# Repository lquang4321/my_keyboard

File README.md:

# Keypad
A standard 17-key numpad in 5x4 config, num lock indicator LED, and a media volume knob. An Arduino Pro Micro (Atmega32u4 5V 16Mhz) is used as the MCU. 
* Author: [Quang Truong](https://github.com/lquang4321) 
* Version: 1 

Make example: 

    make my_keyboard:default
# Schematic

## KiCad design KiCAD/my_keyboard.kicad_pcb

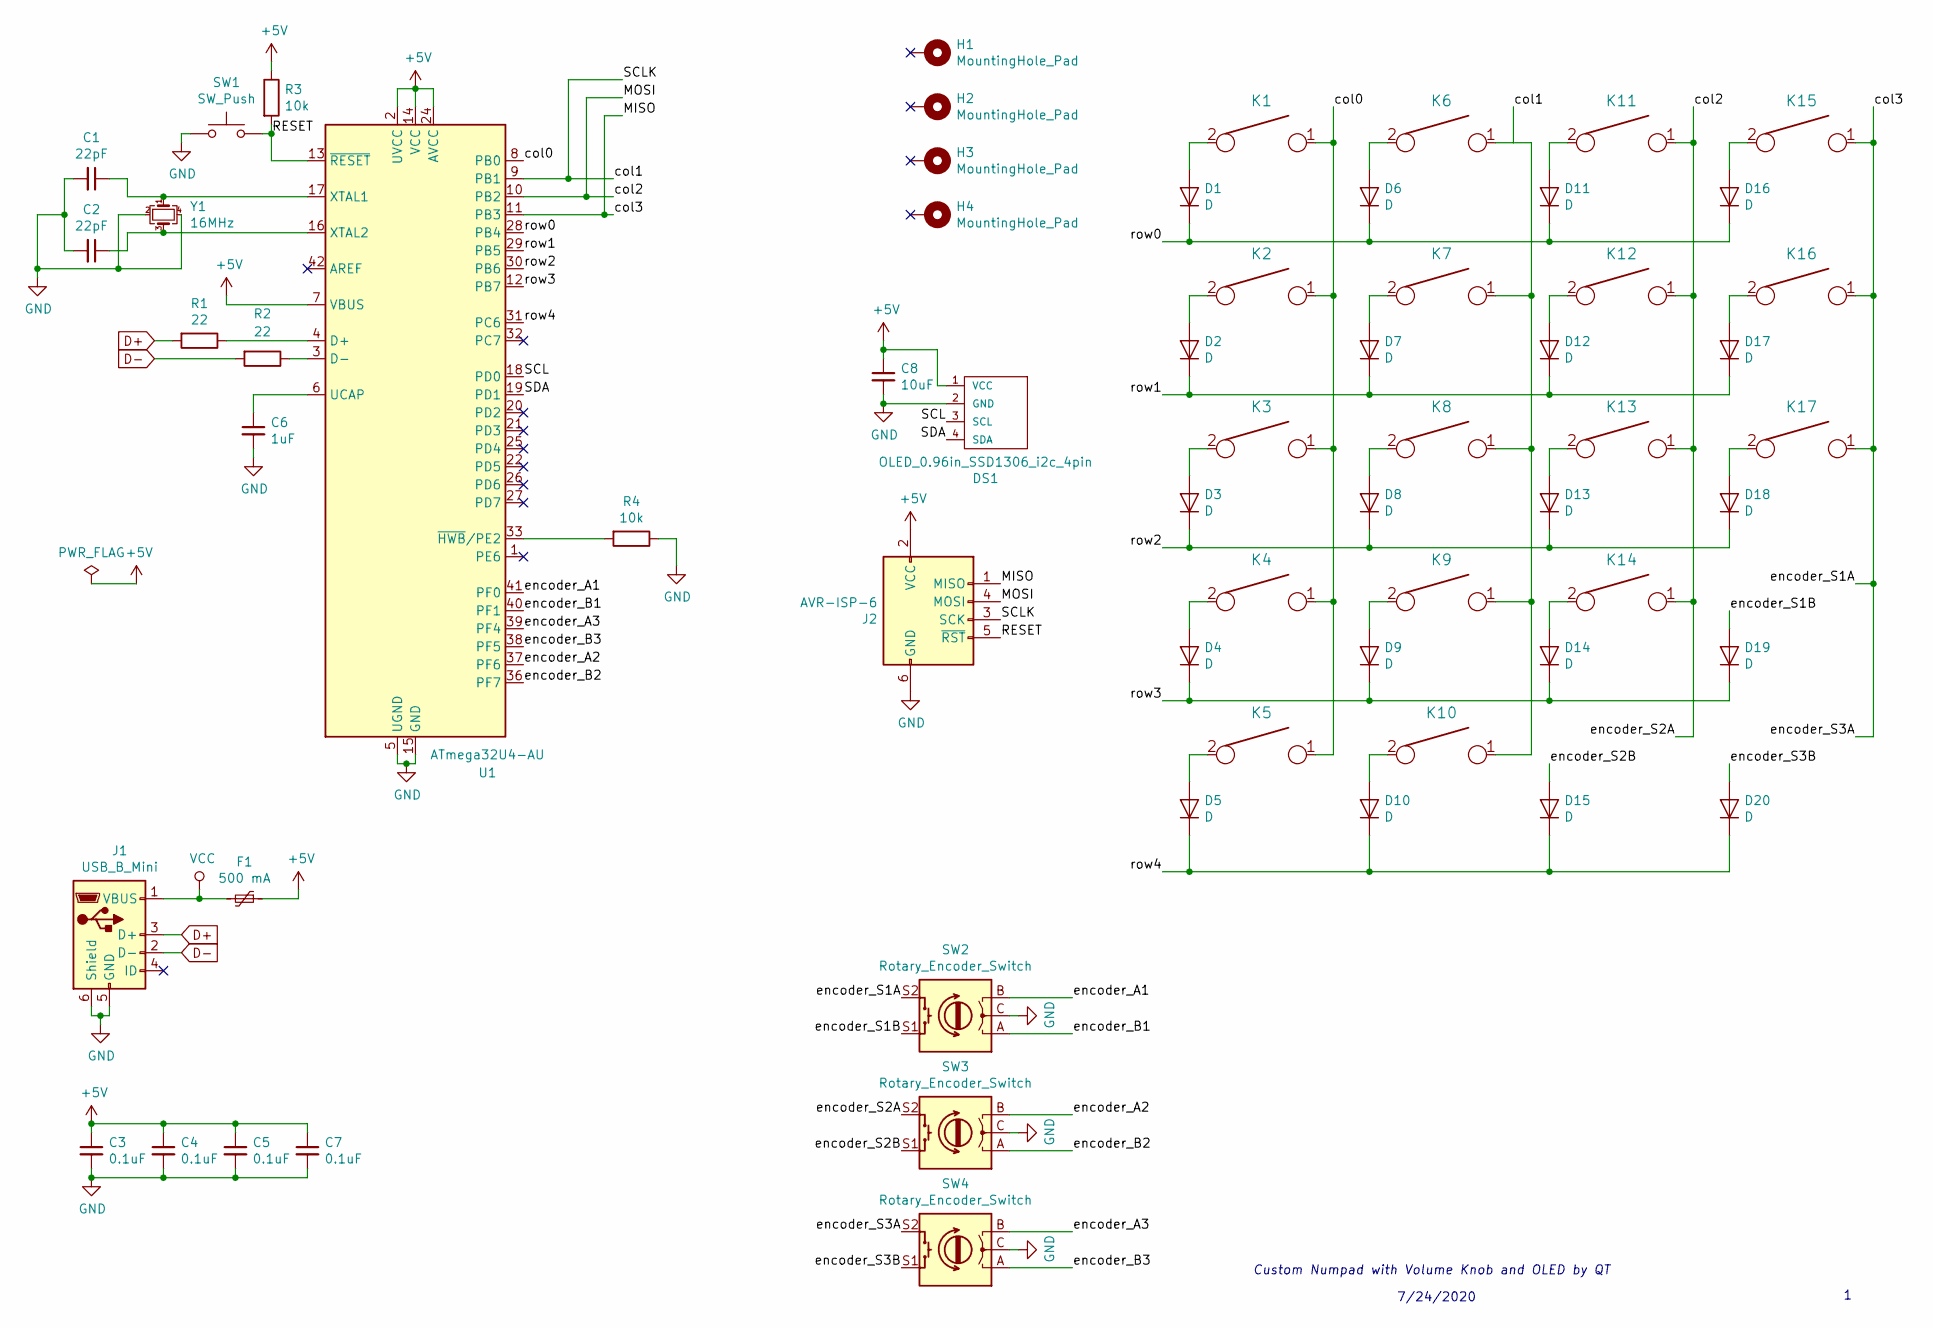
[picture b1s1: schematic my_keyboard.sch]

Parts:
C1, C2: 22pF; C_0805_2012Metric_Pad1.15x1.40mm_HandSolder; JLCPCB Parts C14663
C3, C4, C5, C7: 0.1uF; C_0805_2012Metric_Pad1.15x1.40mm_HandSolder; JLCPCB Parts C14663
C6: 1uF; C_0805_2012Metric_Pad1.15x1.40mm_HandSolder; JLCPCB Parts C15849
C8: 10uF; C_0805_2012Metric_Pad1.15x1.40mm_HandSolder; JLCPCB Parts C19702
D1, D2, D3, D4, D5, D6, D7, D8, D9, D10, D11, D12, D13, D14, D15, D16, D17, D18, D19, D20: D; D_SOD-123; JLCPCB Parts C81598
DS1: OLED_0.96in_SSD1306_i2c_4pin
F1: 500 mA; Fuse_1206_3216Metric_Pad1.42x1.75mm_HandSolder; JLCPCB Parts C151162
H1, H2, H3, H4: MountingHole_Pad; MountingHole_3.2mm_M3_Pad_Via
J1: USB_B_Mini; USB_miniB
J2: AVR-ISP-6; AVR_ICSP_3x2
K1, K2, K3, K4, K6, K7, K8, K9, K10, K11, K12, K13, K14, K15: KEYSW; SW_Cherry_MX_1.00u_PCB
K5: KEYSW; SW_Cherry_MX_2.00u_Plate
K16, K17: KEYSW; SW_Cherry_MX_2.00u_Vertical_Plate
R1, R2: 22; R_0805_2012Metric_Pad1.15x1.40mm_HandSolder; JLCPCB Parts C23345
R3, R4: 10k; R_0805_2012Metric_Pad1.15x1.40mm_HandSolder; JLCPCB Parts C25804
SW1: SW_Push; SW_PUSH_4_5.1x5.1mm; JLCPCB Parts C318884
SW2, SW3, SW4: Rotary_Encoder_Switch; RotaryEncoder_Alps_EC11E-Switch_Vertical_H20mm
U1: ATmega32U4-AU; TQFP-44_10x10mm_P0.8mm; JLCPCB Parts C44854
Y1: 16MHz; Crystal_SMD_3225-4Pin_3.2x2.5mm_HandSoldering; JLCPCB Parts C13738

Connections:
+5V: C3.1, C4.1, C5.1, C7.1, C8.1, DS1.1 (VCC), F1.1, J2.2 (VCC), R3.1, U1.2 (UVCC), U1.7 (VBUS), U1.14 (VCC), U1.24 (AVCC), U1.34 (VCC), U1.44 (AVCC)
/MISO: J2.1 (MISO), K15.1, K16.1, K17.1, SW2.S2, SW4.S2, U1.11 (PB3)
/MOSI: J2.4 (MOSI), K11.1, K12.1, K13.1, K14.1, SW3.S2, U1.10 (PB2)
/RESET: J2.5 (~RST), R3.2, SW1.2, U1.13 (~RESET)
/SCL: DS1.3 (SCL), U1.18 (PD0)
/SCLK: J2.3 (SCK), K6.1, K7.1, K8.1, K9.1, K10.1, U1.9 (PB1)
/SDA: DS1.4 (SDA), U1.19 (PD1)
/col0: K1.1, K2.1, K3.1, K4.1, K5.1, U1.8 (PB0)
/encoder_A1: SW2.B, U1.41 (PF0)
/encoder_A2: SW3.B, U1.37 (PF6)
/encoder_A3: SW4.B, U1.39 (PF4)
/encoder_B1: SW2.A, U1.40 (PF1)
/encoder_B2: SW3.A, U1.36 (PF7)
/encoder_B3: SW4.A, U1.38 (PF5)
/encoder_S1B: D19.2 (A), SW2.S1
/encoder_S2B: D15.2 (A), SW3.S1
/encoder_S3B: D20.2 (A), SW4.S1
/row0: D1.1 (K), D6.1 (K), D11.1 (K), D16.1 (K), U1.28 (PB4)
/row1: D2.1 (K), D7.1 (K), D12.1 (K), D17.1 (K), U1.29 (PB5)
/row2: D3.1 (K), D8.1 (K), D13.1 (K), D18.1 (K), U1.30 (PB6)
/row3: D4.1 (K), D9.1 (K), D14.1 (K), D19.1 (K), U1.12 (PB7)
/row4: D5.1 (K), D10.1 (K), D15.1 (K), D20.1 (K), U1.31 (PC6)
D+: J1.3 (D+), R1.2
D-: J1.2 (D-), R2.2
GND: C1.2, C2.2, C3.2, C4.2, C5.2, C6.2, C7.2, C8.2, DS1.2 (GND), J1.5 (GND), J1.6 (Shield), J2.6 (GND), R4.1, SW1.1, SW2.C, SW3.C, SW4.C, U1.5 (UGND), U1.15 (GND), U1.23 (GND), U1.35 (GND), U1.43 (GND), Y1.2, Y1.4
unnamed: C1.1, U1.17 (XTAL1), Y1.1
unnamed: C2.1, U1.16 (XTAL2), Y1.3
unnamed: C6.1, U1.6 (UCAP)
unnamed: D1.2 (A), K1.2
unnamed: D2.2 (A), K2.2
unnamed: D3.2 (A), K3.2
unnamed: D4.2 (A), K4.2
unnamed: D5.2 (A), K5.2
unnamed: D6.2 (A), K6.2
unnamed: D7.2 (A), K7.2
unnamed: D8.2 (A), K8.2
unnamed: D9.2 (A), K9.2
unnamed: D10.2 (A), K10.2
unnamed: D11.2 (A), K11.2
unnamed: D12.2 (A), K12.2
unnamed: D13.2 (A), K13.2
unnamed: D14.2 (A), K14.2
unnamed: D16.2 (A), K15.2
unnamed: D17.2 (A), K16.2
unnamed: D18.2 (A), K17.2
unnamed: R1.1, U1.4 (D+)
unnamed: R2.1, U1.3 (D-)
unnamed: R4.2, U1.33 (~HWB~/PE2)
VCC: F1.2, J1.1 (VBUS)

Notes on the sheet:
Custom Numpad with Volume Knob and OLED by QT
7/24/2020

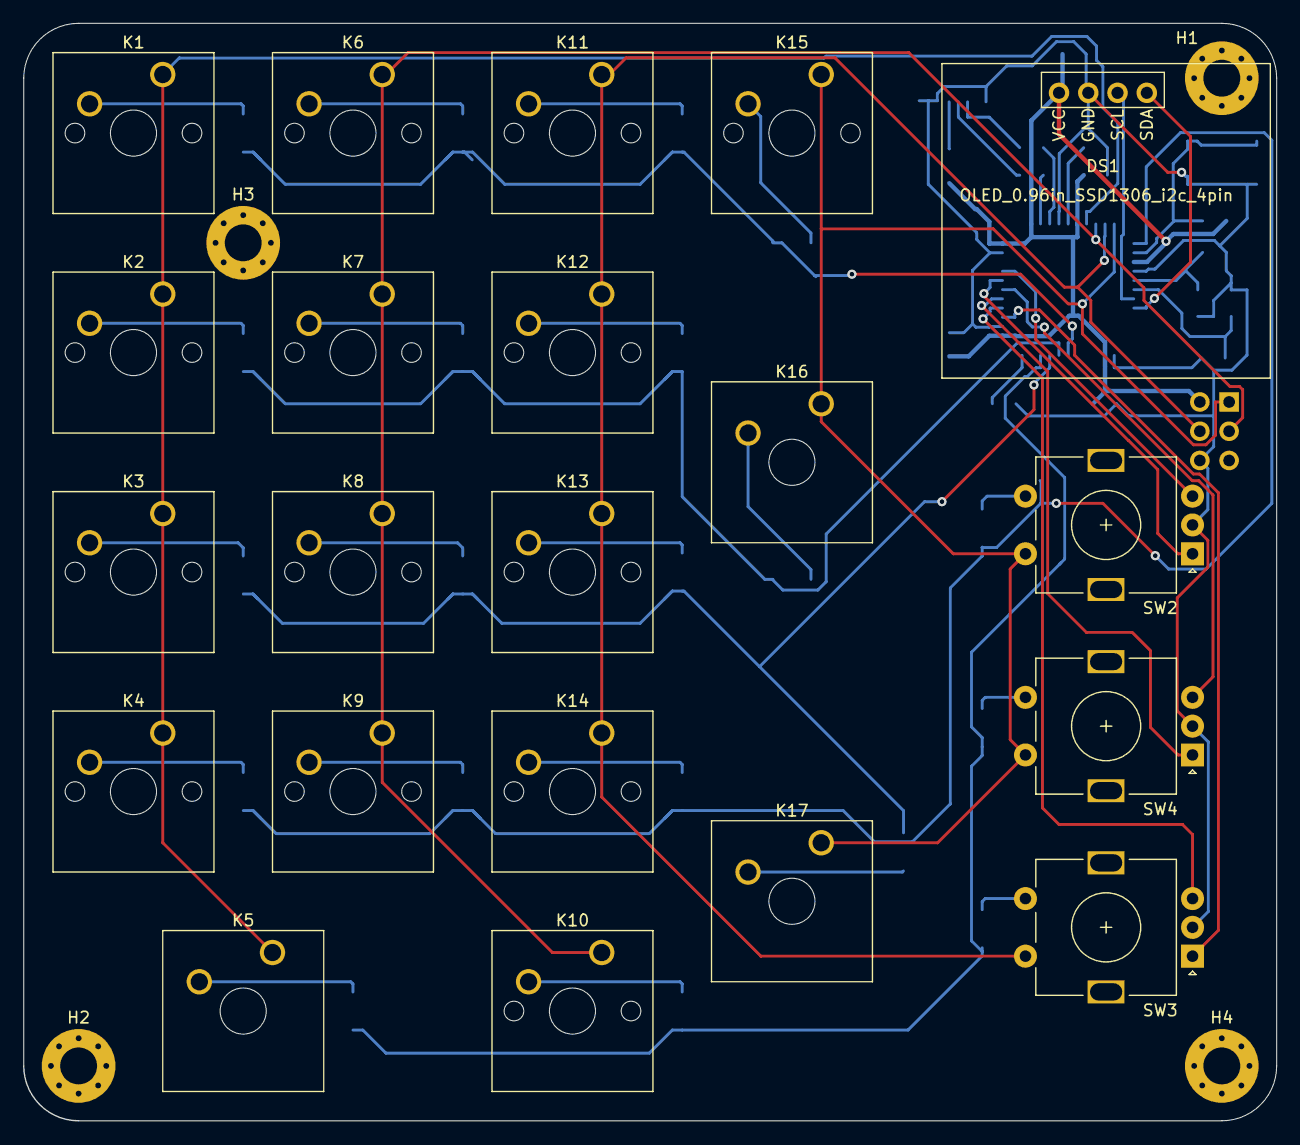
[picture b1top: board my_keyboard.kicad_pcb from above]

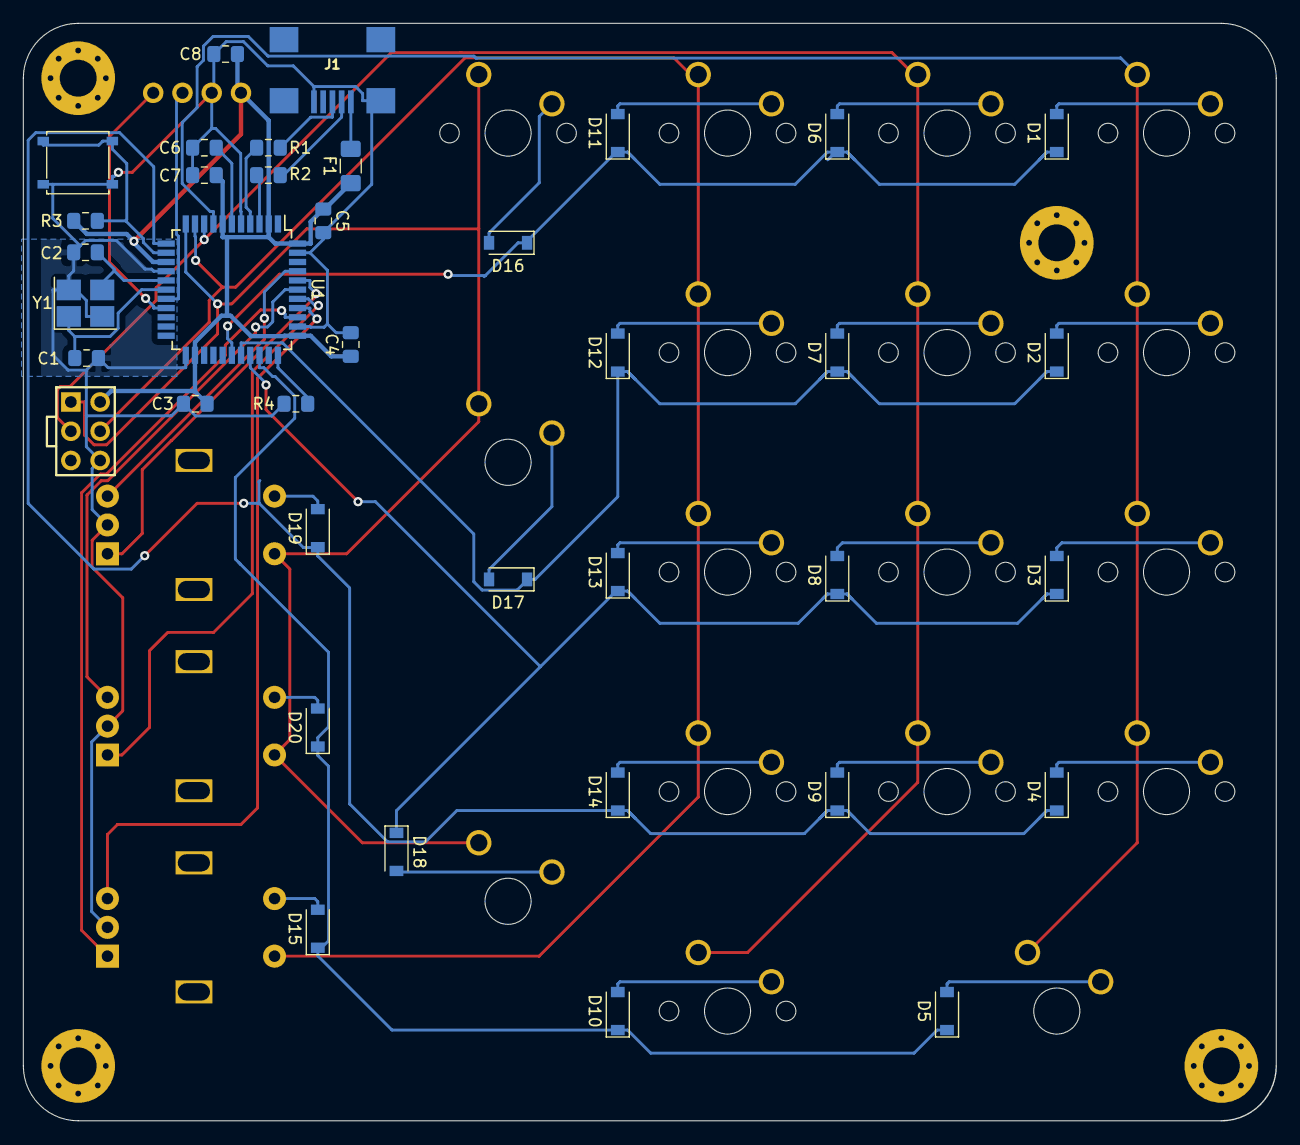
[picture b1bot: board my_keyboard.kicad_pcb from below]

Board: 2 copper layers, 108.7 x 95.2 mm, 63 parts (38 on the bottom side), 49 nets.

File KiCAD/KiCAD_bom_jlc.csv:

"Comment","Designator","Footprint","LCSC Part #"
"22pF","C1,C2","C_0805_2012Metric_Pad1.15x1.40mm_HandSolder","C14663"
"0.1uF","C3,C4,C5,C7","C_0805_2012Metric_Pad1.15x1.40mm_HandSolder","C14663"
"1uF","C6","C_0805_2012Metric_Pad1.15x1.40mm_HandSolder","C15849"
"10uF","C8","C_0805_2012Metric_Pad1.15x1.40mm_HandSolder","C19702"
"D","D1,D16,D11,D6,D17,D12,D7,D2,D18,D13,D8,D3,D19,D14,D9,D4,D20,D15,D10,D5","D_SOD-123","C81598"
"500 mA","F1","Fuse_1206_3216Metric_Pad1.42x1.75mm_HandSolder","C151162"
"22","R1,R2","R_0805_2012Metric_Pad1.15x1.40mm_HandSolder","C23345"
"10k","R4,R3","R_0805_2012Metric_Pad1.15x1.40mm_HandSolder","C25804"
"SW_Push","SW1","SW_PUSH_4_5.1x5.1mm","C318884"
"ATmega32U4-AU","U1","TQFP-44_10x10mm_P0.8mm","C44854"
"16MHz","Y1","Crystal_SMD_3225-4Pin_3.2x2.5mm_HandSoldering","C13738"

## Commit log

2020-08-17 Create repository
2020-08-17 Organized Folder
2020-08-17 Added QMK Codes
2020-08-18 Update PCB
2020-08-18 Added KiCAD Library
2020-08-18 Updated KiCAD Lib
2020-08-18 Updated KiCAD Schem
2020-08-18 Fixed Diode Issue
    Previously used wrong diode symbol meant for simulation not design.
2020-08-18 Finalized Prototype PCB
    Due to the cramp nature around the MCU chip, I resorted to using Freerouting to autoroute all the complexity.
2020-08-18 Generated Gerber Files
2020-08-18 Renamed due to errors with space
2020-08-18 Update stuff
2020-08-19 Added PDF
2020-08-19 Added Schematic screenshot
